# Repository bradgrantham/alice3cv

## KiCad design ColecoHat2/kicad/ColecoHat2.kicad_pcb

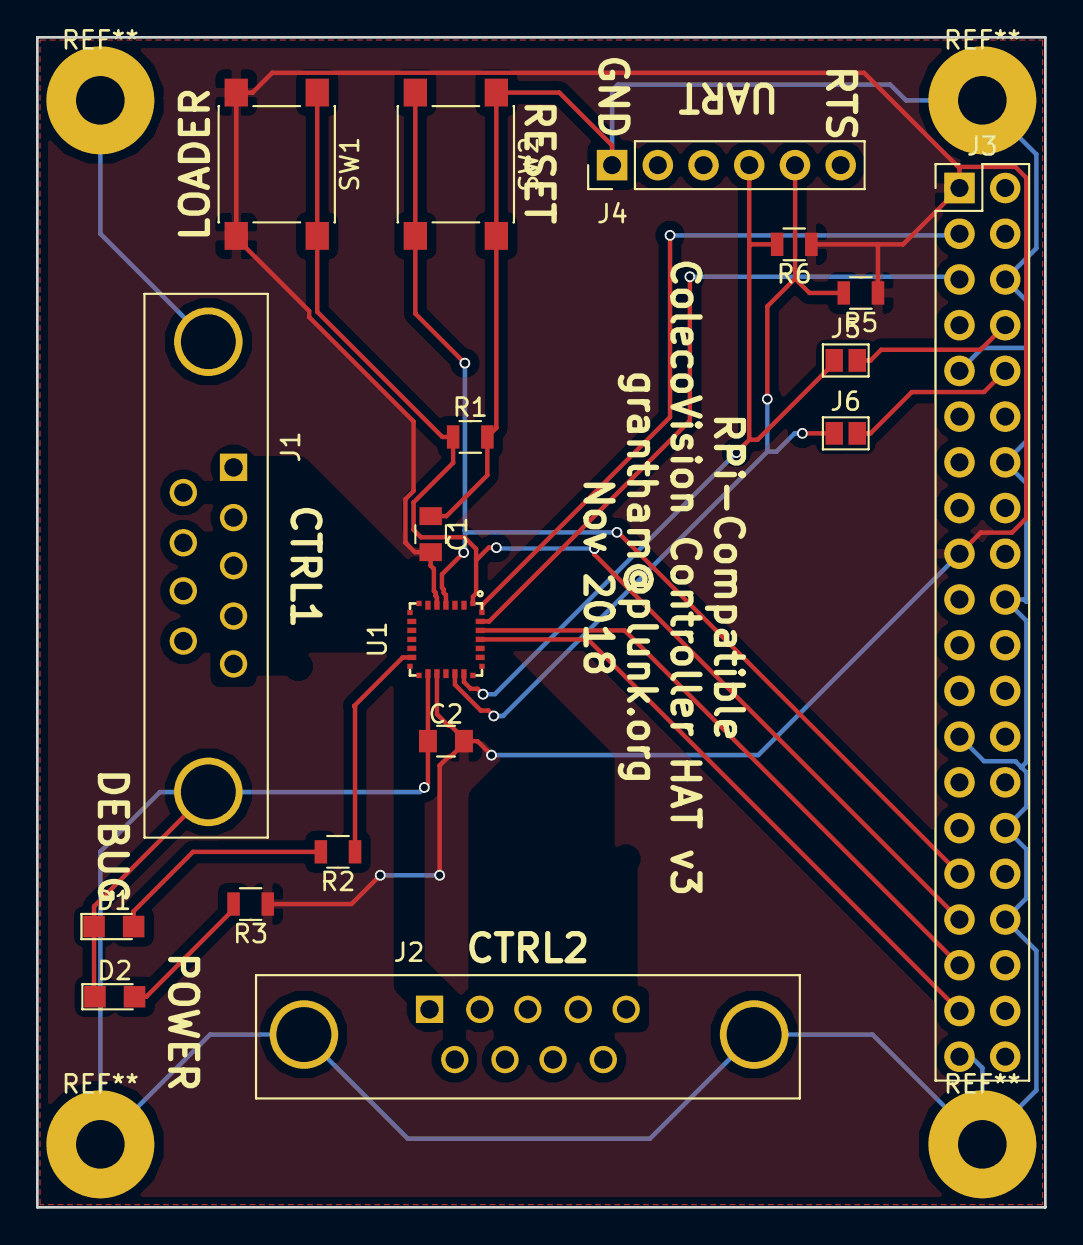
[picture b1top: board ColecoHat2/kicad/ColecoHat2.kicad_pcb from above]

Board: 2 copper layers, 56.0 x 65.0 mm, 18 parts (0 on the bottom side), 31 nets.

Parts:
C1, C2: 100nF; C_0805
D1: DEBUG; LED_0805
D2: POWER; LED_0805
J1: CTRL1; DB9MD
J2: CTRL2; DB9MD
J3: PI_HEADER; Pin_Header_Straight_2x20_Pitch2.54mm
J4: CONN_01X06; Pin_Header_Straight_1x06_Pitch2.54mm
J5, J6: GS2
R1: 10k; R_0805
R2: 470; R_0805
R3: 1K; R_0805
R5, R6: 100k; R_0805
SW1: BOOTLOADER; SW_SPST_PTS645
SW2: RESET; SW_SPST_PTS645
U1: STM32L011G4U6; UFQFPN-28

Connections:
+3V3: C1.2, C2.2, J3.1, J3.17, R3.1, R5.1, R6.1, SW1.2, U1.5, U1.17
BOOTLOADER: J3.33, R1.1, SW1.1, U1.1
DEBUG_GPIO: J3.37, U1.25
DEBUG_LED: R2.1, U1.13
E1: J1.4, U1.11
E2: J2.4, U1.23
FIRE1: J1.6, U1.7
FIRE2: J2.6, U1.15
GND: C1.1, C2.1, D1.1, D2.1, J1.0, J2.0, J3.6, J3.9, J3.14, J3.20, J3.25, J3.30, J3.34, J3.39, J4.1, R1.2, SW2.1, U1.16
I2C1_SCL: J3.5, U1.27
I2C1_SDA: J3.3, U1.28
IRQ: J3.35, U1.26
N1: J1.1, U1.6
N2: J2.1, U1.14
NRST: J3.31, SW2.2, U1.4
unnamed: D1.2, R2.2
unnamed: D2.2, R3.2
unnamed: J3.8, J5.2
unnamed: J3.10, J6.2
QUADA1: J1.7, U1.9
QUADA2: J2.7, U1.21
QUADB1: J1.9, U1.12
QUADB2: J2.9, U1.24
S1: J1.2, U1.8
S2: J2.2, U1.18
SELECT_JOYSTICK: J1.8, J2.8, U1.2
SELECT_KEYPAD: J1.5, J2.5, U1.3
USART1_RX: J4.4, J5.1, R6.2, U1.20
USART1_TX: J4.5, J6.1, R5.2, U1.19
W1: J1.3, U1.10
W2: J2.3, U1.22

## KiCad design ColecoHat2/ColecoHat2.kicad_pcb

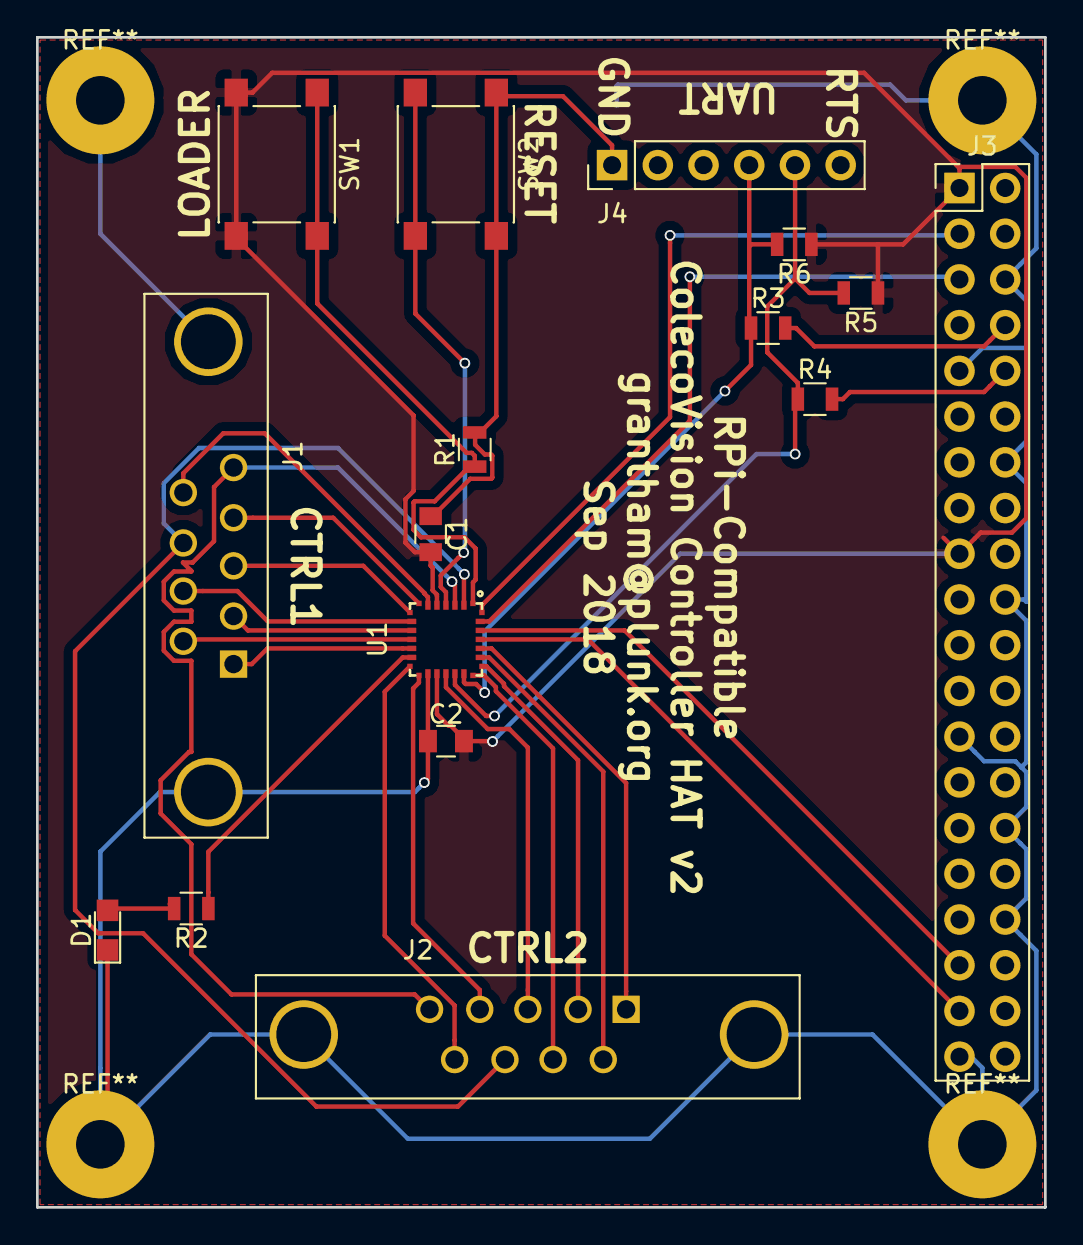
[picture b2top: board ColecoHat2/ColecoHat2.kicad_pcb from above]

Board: 2 copper layers, 56.0 x 65.0 mm, 16 parts (0 on the bottom side), 30 nets.

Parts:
C1, C2: 100nF; C_0805
D1: DEBUG LED; LED_0805
J1: CTRL1; DB9FD
J2: CTRL2; DB9FD
J3: PI_HEADER; Pin_Header_Straight_2x20_Pitch2.54mm
J4: CONN_01X06; Pin_Header_Straight_1x06_Pitch2.54mm
R1: 10k; R_0805
R2: 220; R_0805
R3, R4: 0; R_0805
R5, R6: 100k; R_0805
SW1: BOOTLOADER; SW_SPST_PTS645
SW2: RESET; SW_SPST_PTS645
U1: STM32L011G4U6; UFQFPN-28

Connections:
+3V3: C1.2, C2.2, J3.1, J3.17, R5.1, R6.1, SW1.2, U1.5, U1.17
BOOTLOADER: R1.1, SW1.1, U1.1
DEBUG_GPIO: J3.37, U1.25
DEBUG_LED: R2.1, U1.13
E1: J1.4, U1.7
E2: J2.4, U1.15
FIRE1: J1.6, U1.11
FIRE2: J2.6, U1.23
GND: C1.1, C2.1, D1.1, J1.0, J2.0, J3.6, J3.9, J3.14, J3.20, J3.25, J3.30, J3.34, J3.39, J4.1, R1.2, SW2.1, U1.16
I2C1_SCL: J3.5, U1.27
I2C1_SDA: J3.3, U1.28
IRQ: J3.35, U1.26
N1: J1.1, U1.12
N2: J2.1, U1.24
unnamed: D1.2, R2.2
unnamed: J3.8, R3.2
unnamed: J3.10, R4.2
unnamed: SW2.2, U1.4
QUADA1: J1.7, U1.9
QUADA2: J2.7, U1.21
QUADB1: J1.9, U1.6
QUADB2: J2.9, U1.14
S1: J1.2, U1.10
S2: J2.2, U1.22
SELECT_JOYSTICK: J1.8, J2.8, U1.2
SELECT_KEYPAD: J1.5, J2.5, U1.3
USART1_RX: J4.4, R3.1, R6.2, U1.20
USART1_TX: J4.5, R4.1, R5.2, U1.19
W1: J1.3, U1.8
W2: J2.3, U1.18

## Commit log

2018-09-29 Initial commit
    ColecoHat HAT for CV controllers
    dostuff.cpp makes binary images into bitmaps
2018-09-29 Rename KiCAD files for 2nd version of HAT
2018-10-01 update to PCB and BOM fields
2018-10-01 Remove generated file
2018-10-04 add pull-ups for UART
2018-10-27 add STM32L0 STM32L011G4U6 component
2018-10-27 move KiCAD bits into kicad subdirectory
2018-10-28 add initial bits for ARM firmware
2018-10-29 shrink heap
2018-11-04 print whichever direction or FIRE1 is being pushed
    Add synchronous UART support
    Shrink heap to 0 (to fit .data and .bss and stack)
    Set and read joystick pins
2018-11-05 read keypad and right FIRE, serial now 115200 baud
2018-11-05 extract functions for controller probing
2018-11-05 beginnings of controller 2
2018-11-19 add scripts for controlling cvhat from RPi
2018-11-19 set estack correctly and reduce required heap alignment
2018-11-19 make FLASH script executable
2018-11-19 make another stab at controller #2, document better
2018-11-25 extract TUPLE, provide RasPi directories
2018-11-25 add i2c initial stabs
2018-11-25 quiet i2c debugging
2018-11-25 remove some i2c dead code
2018-11-25 pass controllers over i2c
2018-12-31 add larger STM32L041K6U6 component
2018-12-31 remove because copyrighted
2018-12-31 start a new linker script
